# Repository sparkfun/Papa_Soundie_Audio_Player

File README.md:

SparkFun Papa Soundie Audio Player
========================================

[*Papa Soundie Audio Player (14554)*](https://www.sparkfun.com/products/14554)

The SparkFun Papa Soundie is an audio playback device breaking out VS1000D audio codec IC allowing this little board the ability to decode OGG Vorbis and WAV type files. With an SD card for sound storage and a built-in ATmega328P programmed with Arduino you’ll be adding custom sound effects to your project with less hardware and in a familiar programming environment.

The Papa Soundie is the upgraded version of the Little Soundie with similar areas that allow you, the user, to interact with the board but with more customizable options. The top section of this board contains the Arduino Controls. We’ve broken out 2 analog input pins and 7 digital pins, which includes three PWM pins, SPI and I2C communication pins on the ATMEGA328P to easily control audio playback using sensors and other input.

Up to 32 files can be triggered to play from a micro SD card allowing for more storage space than that allowed on the Little Soundie. To play the audio stored in the SD card, plug in a powered speaker to the 3.5mm jack, upload an Arduino sketch the uses the Papa Soundie library, and start jammin'.

_Note: Speakers are required for the Papa Soundie, not headphones. Headphones won’t break anything but you won’t get any sound either._

Repository Contents
-------------------

* **/Documentation** - Data sheets, additional product information
* **/Enclosure** - Enclosure files 
* **/Firmware** - Example code 
* **/Hardware** - Eagle design files (.brd, .sch)
* **/Libraries** - Libraries for use with the Papa Soundie
* **/Production** - Production panel files (.brd)
* **/Software** - Related software for the Papa Soundie

Documentation
--------------
* **[Library](https://github.com/sparkfun/Papa_Soundie_Audio_Player)** - <C> library for the Papa Soundie.
* **[Hookup Guide](https://learn.sparkfun.com/tutorials/papa-soundie-audio-player-hookup-guide)** - Basic hookup guide for the Papa Soundie.
* **[SparkFun Fritzing repo](https://github.com/sparkfun/Fritzing_Parts)** - Fritzing diagrams for SparkFun products.
* **[SparkFun 3D Model repo](https://github.com/sparkfun/3D_Models)** - 3D models of SparkFun products. 
* **[SparkFun Graphical Datasheets](https://github.com/sparkfun/Graphical_Datasheets)** -Graphical Datasheets for various SparkFun products.

License Information
-------------------

This product is _**open source**_! 

Please review the LICENSE.md file for license information. 

If you have any questions or concerns on licensing, please contact techsupport@sparkfun.com.

Distributed as-is; no warranty is given.

- Your friends at SparkFun.

_<COLLABORATION CREDIT>_

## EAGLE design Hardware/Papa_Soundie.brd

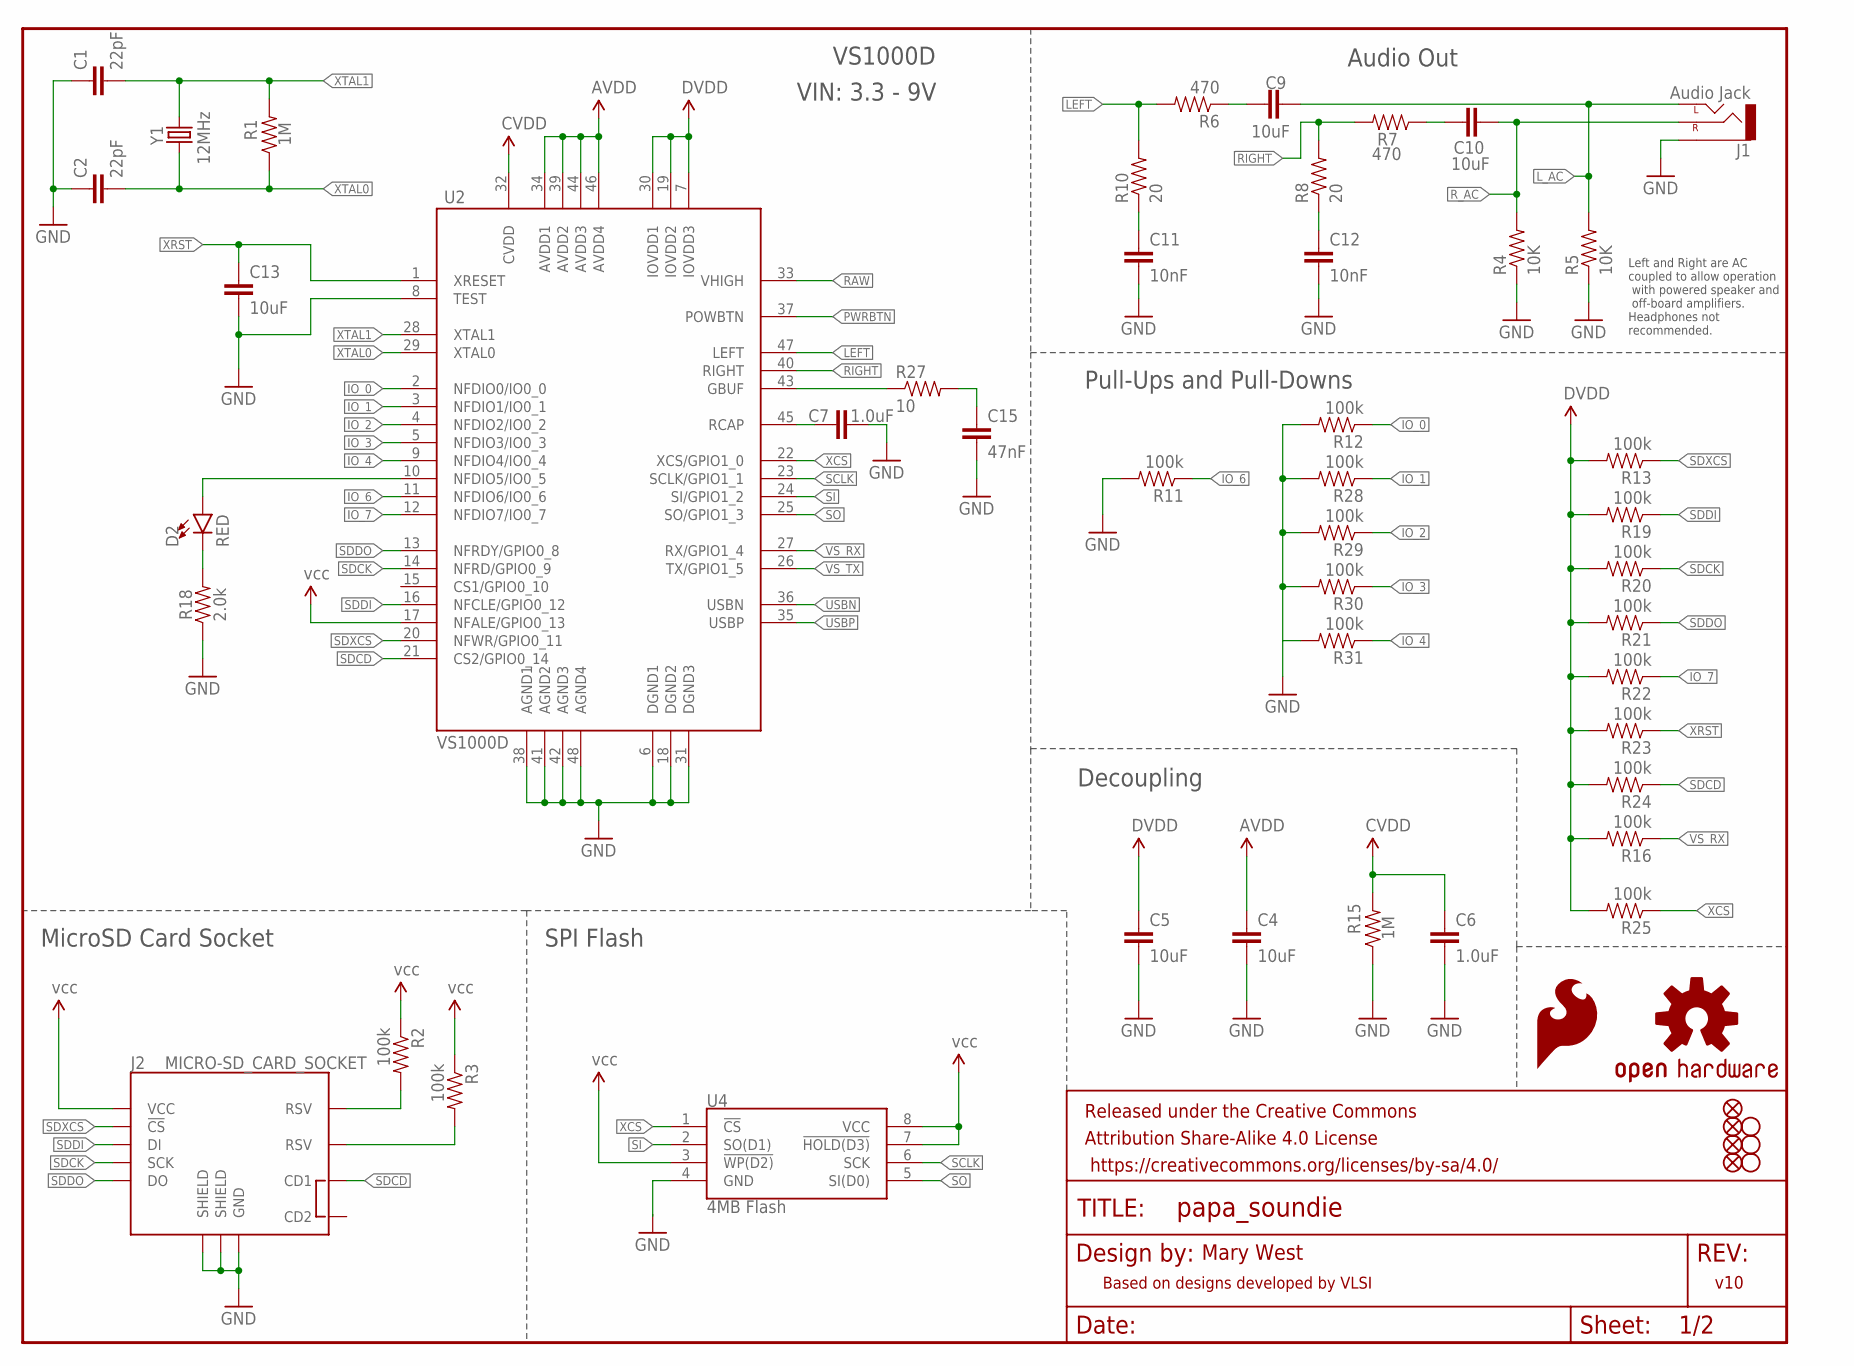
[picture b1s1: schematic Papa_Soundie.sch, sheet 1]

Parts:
C1, C2: 22pF; 0603-CAP
C4, C5: 10uF; 0603
C6, C7: 1.0uF; 0603-CAP
C9, C10, C13: 10uF; 0603-CAP
C11, C12: 10nF; 0603-CAP
C15: 47nF; 0603-CAP
D2: RED; LED-0603
FD1, FD2, FD3, FD4: FIDUCIALUFIDUCIAL; FIDUCIAL-MICRO
FRAME1: FRAME-LETTER; CREATIVE_COMMONS
H1, H2, H3: STAND-OFFTIGHT; STAND-OFF-TIGHT
J1: Audio Jack; AUDIO-JACK-3.5MM-SMD
J2: MICRO-SD_CARD_SOCKET; MICRO-SD-SOCKET
LOGO1: OSHW-LOGOL; OSHW-LOGO-L
LOGO2: SFE_LOGO_FLAME.2_INCH; SFE_LOGO_FLAME_.2
R1, R15: 1M; 0603-RES
R2, R3, R11, R12, R13, R16, R19, R20, R21, R22, R23, R24, R25, R28, R29, R30, R31: 100k; 0603-RES
R4, R5: 10K; 0603-RES
R6, R7: 470; 0603-RES
R8, R10: 20; 0603-RES
R18: 2.0k; 0603
R27: 10; 0603-RES
U2: VS1000D; LQFP-48
U4: 4MB Flash; SO08
Y1: 12MHz; CRYSTAL-SMD-5X3

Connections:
AVDD: C4.1, U2.34 (AVDD1), U2.39 (AVDD2), U2.44 (AVDD3), U2.46 (AVDD4)
CVDD: C6.1, R15.2, U2.32 (CVDD)
DVDD: C5.1, R13.2, R16.2, R19.2, R20.2, R21.2, R22.2, R23.2, R24.2, R25.2, U2.7 (IOVDD3), U2.19 (IOVDD2), U2.30 (IOVDD1)
GBUF: R27.1, U2.43 (GBUF)
GND: C1.1, C2.1, C4.2, C5.2, C6.2, C7.2, C11.2, C12.2, C13.2, C15.2, J1.SLEEVE, J2.GND, J2.GND1 (SHIELD), J2.GND3 (SHIELD), R4.1, R5.1, R11.2, R12.2, R15.1, R18.1, R28.2, R29.2, R30.2, R31.2, U2.6 (DGND1), U2.8 (TEST), U2.18 (DGND2), U2.31 (DGND3), U2.38 (AGND1), U2.41 (AGND2), U2.42 (AGND3), U2.48 (AGND4), U4.4 (GND); also elsewhere on the board
IO_0: R12.1, U2.2 (NFDIO0/IO0_0); also elsewhere on the board
IO_1: R28.1, U2.3 (NFDIO1/IO0_1); also elsewhere on the board
IO_2: R29.1, U2.4 (NFDIO2/IO0_2); also elsewhere on the board
IO_3: R30.1, U2.5 (NFDIO3/IO0_3); also elsewhere on the board
IO_4: R31.1, U2.9 (NFDIO4/IO0_4); also elsewhere on the board
IO_6: R11.1, U2.11 (NFDIO6/IO0_6)
IO_7: R22.1, U2.12 (NFDIO7/IO0_7)
LEFT: R6.2, R10.2, U2.47 (LEFT)
L_AC: C9.2, J1.TIP (LEFT), R5.2; also elsewhere on the board
unnamed: C15.1, R27.2
unnamed: C9.1, R6.1
unnamed: C11.1, R10.1
unnamed: C7.1, U2.45 (RCAP)
unnamed: J2.RSV1 (RSV), R2.2
unnamed: C10.1, R7.1
unnamed: J2.RSV2 (RSV), R3.2
unnamed: C12.1, R8.1
unnamed: D2.C, R18.2
unnamed: D2.A, U2.10 (NFDIO5/IO0_5)
PWRBTN: U2.37 (POWBTN); also elsewhere on the board
RAW: U2.33 (VHIGH); also elsewhere on the board
RIGHT: R7.2, R8.2, U2.40 (RIGHT)
R_AC: C10.2, J1.RING (RIGHT), R4.2; also elsewhere on the board
SCLK: U2.23 (SCLK/GPIO1_1), U4.6 (SCK)
SDCD: J2.CD1, R24.1, U2.21 (CS2/GPIO0_14)
SDCK: J2.SCLK (SCK), R20.1, U2.14 (NFRD/GPIO0_9)
SDDI: J2.DI, R19.1, U2.16 (NFCLE/GPIO0_12)
SDDO: J2.DO, R21.1, U2.13 (NFRDY/GPIO0_8)
SDXCS: J2.CS (!CS), R13.1, U2.20 (NFWR/GPIO0_11)
SI: U2.24 (SI/GPIO1_2), U4.2 (SO(D1))
SO: U2.25 (SO/GPIO1_3), U4.5 (SI(D0))
USBN: U2.36 (USBN); also elsewhere on the board
USBP: U2.35 (USBP); also elsewhere on the board
VCC: J2.VCC, R2.1, R3.1, U2.17 (NFALE/GPIO0_13), U4.3 (!WP(D2)), U4.7 (!HOLD(D3)), U4.8 (VCC); also elsewhere on the board
VS_RX: R16.1, U2.27 (RX/GPIO1_4); also elsewhere on the board
VS_TX: U2.26 (TX/GPIO1_5); also elsewhere on the board
XCS: R25.1, U2.22 (XCS/GPIO1_0), U4.1 (!CS)
XRST: C13.1, R23.1, U2.1 (XRESET)
XTAL0: C2.2, R1.1, U2.29 (XTAL0), Y1.1
XTAL1: C1.2, R1.2, U2.28 (XTAL1), Y1.3 (2)

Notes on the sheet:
Mary West
v10
Decoupling
Left and Right are AC coupled to allow operation with powered speaker and off-board amplifiers. Headphones not recommended.
Based on designs developed by VLSI
Audio Out
MicroSD Card Socket
Pull-Ups and Pull-Downs
SPI Flash
VS1000D
VIN: 3.3 - 9V

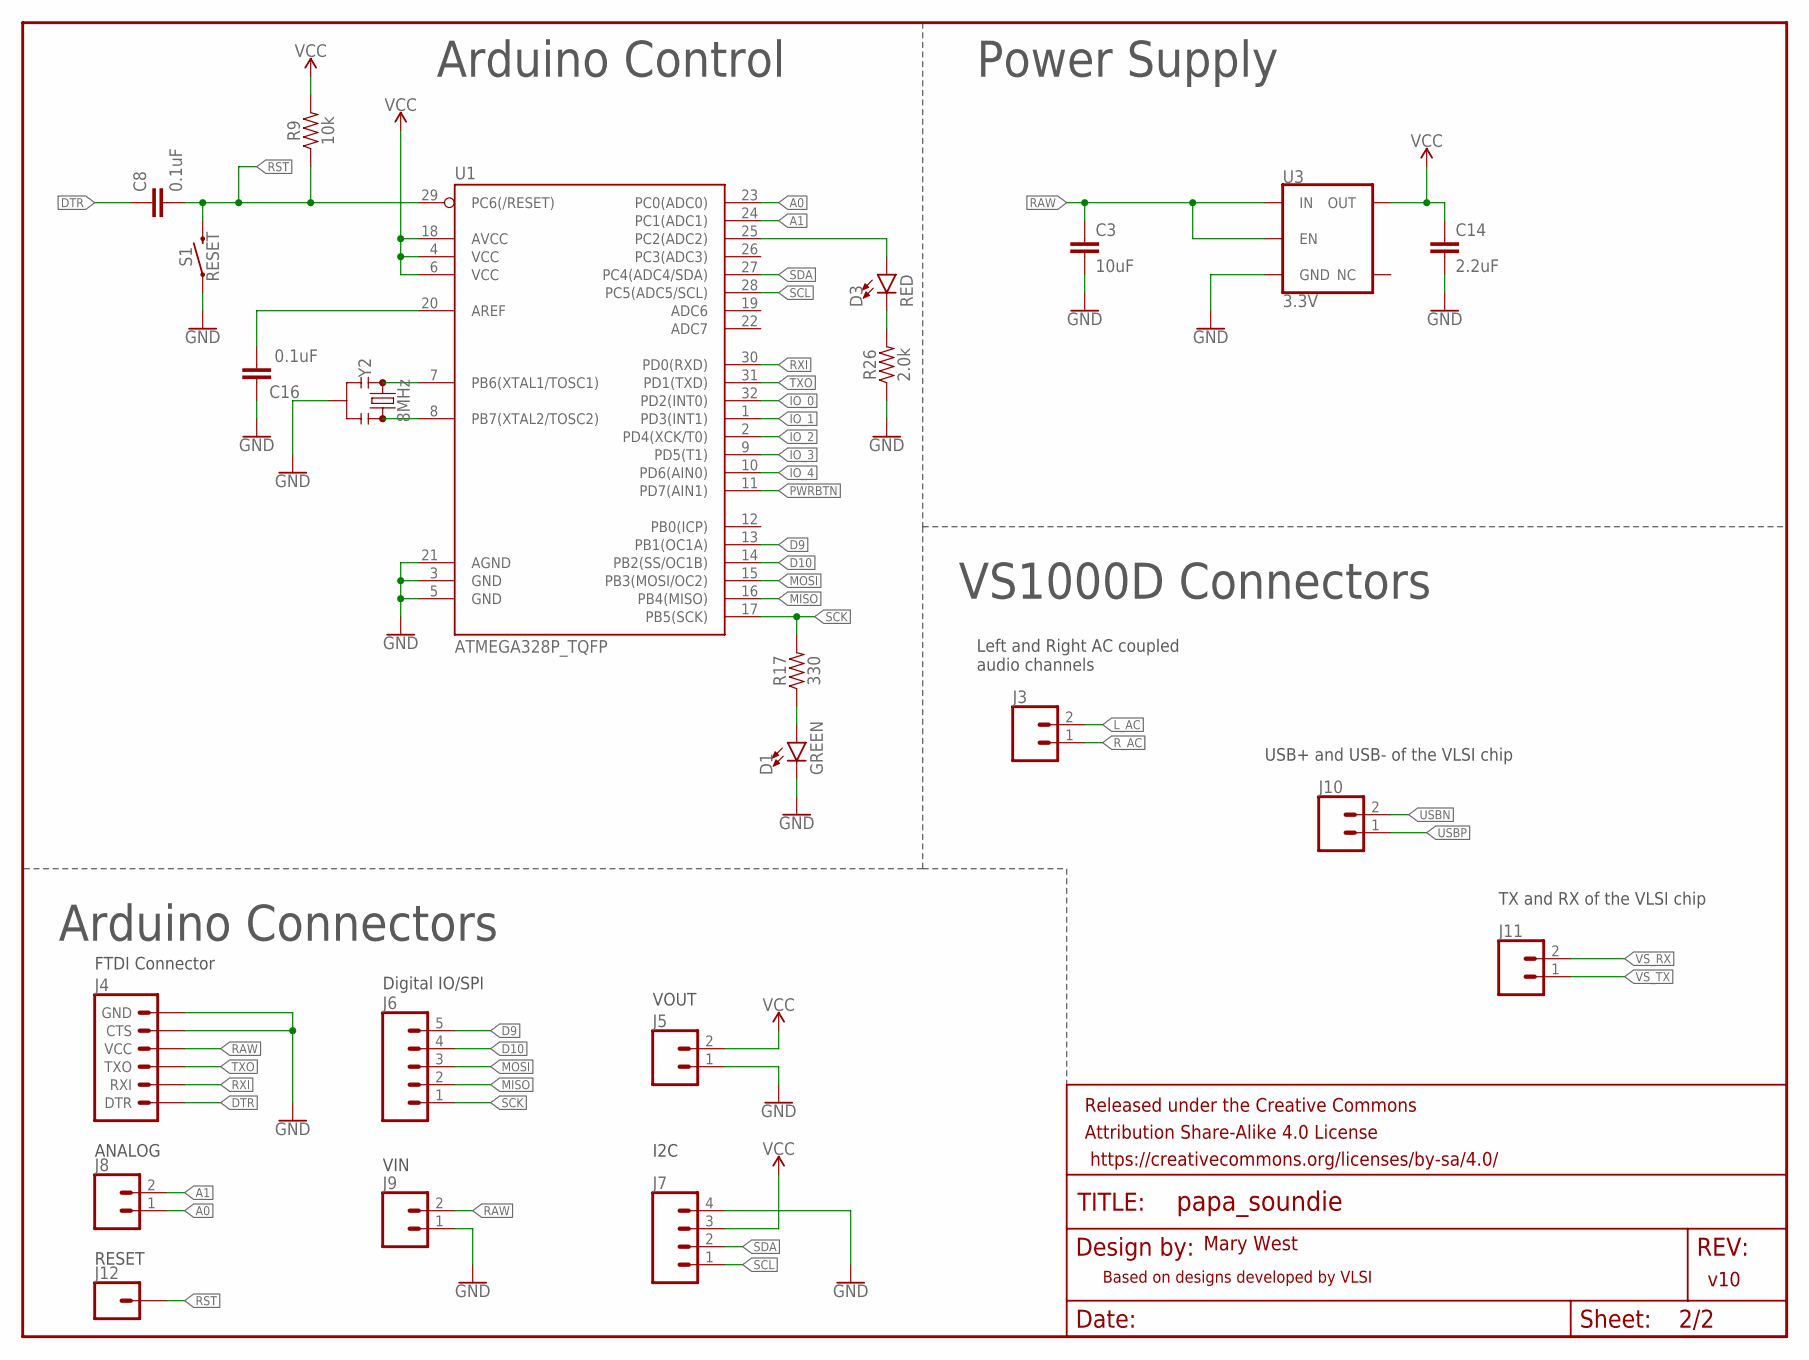
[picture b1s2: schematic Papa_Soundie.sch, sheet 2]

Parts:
C3: 10uF; 0603
C8, C16: 0.1uF; 0603
C14: 2.2uF; 0603
D1: GREEN; LED-0603
D3: RED; LED-0603
FRAME2: FRAME-LETTER; CREATIVE_COMMONS
J3, J5, J8, J9, J10, J11: CONN_02; 1X02
J4: 6_PIN_SERIAL_TARGETSILK; 6_PIN_SERIAL_TARGET_SIDE_W_SILK
J6: CONN_05; 1X05
J7: CONN_04; 1X04
J12: CONN_01; 1X01
R9: 10k; 0603
R17: 330; 0603
R26: 2.0k; 0603
S1: RESET; TACTILE_SWITCH_SMD_5.2MM
U1: ATMEGA328P_TQFP; TQFP32-08
U3: 3.3V; SOT23-5
Y2: 8MHz; RESONATOR-SMD-3.2X1.3

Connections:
A0: J8.1, U1.23 (PC0(ADC0))
A1: J8.2, U1.24 (PC1(ADC1))
D9: J6.5, U1.13 (PB1(OC1A))
D10: J6.4, U1.14 (PB2(SS/OC1B))
DTR: C8.1, J4.P$1 (DTR)
GND: C3.2, C14.2, C16.1, D1.C, J4.P$5 (CTS), J4.P$6 (GND), J5.1, J7.4, J9.1, R26.1, S1.1, U1.3 (GND), U1.5 (GND), U1.21 (AGND), U3.2 (GND), Y2.2; also elsewhere on the board
IO_0: U1.32 (PD2(INT0)); also elsewhere on the board
IO_1: U1.1 (PD3(INT1)); also elsewhere on the board
IO_2: U1.2 (PD4(XCK/T0)); also elsewhere on the board
IO_3: U1.9 (PD5(T1)); also elsewhere on the board
IO_4: U1.10 (PD6(AIN0)); also elsewhere on the board
L_AC: J3.2; also elsewhere on the board
MISO: J6.2, U1.16 (PB4(MISO))
MOSI: J6.3, U1.15 (PB3(MOSI/OC2))
unnamed: U1.7 (PB6(XTAL1/TOSC1)), Y2.1
unnamed: U1.8 (PB7(XTAL2/TOSC2)), Y2.3
unnamed: D3.A, U1.25 (PC2(ADC2))
unnamed: D3.C, R26.2
unnamed: C16.2, U1.20 (AREF)
unnamed: D1.A, R17.1
PWRBTN: U1.11 (PD7(AIN1)); also elsewhere on the board
RAW: C3.1, J4.P$4 (VCC), J9.2, U3.1 (IN), U3.3 (EN); also elsewhere on the board
RST: C8.2, J12.1, R9.1, S1.3 (2), U1.29 (PC6(/RESET))
RXI: J4.P$3 (RXI), U1.30 (PD0(RXD))
R_AC: J3.1; also elsewhere on the board
SCK: J6.1, R17.2, U1.17 (PB5(SCK))
SCL: J7.1, U1.28 (PC5(ADC5/SCL))
SDA: J7.2, U1.27 (PC4(ADC4/SDA))
TXO: J4.P$2 (TXO), U1.31 (PD1(TXD))
USBN: J10.2; also elsewhere on the board
USBP: J10.1; also elsewhere on the board
VCC: C14.1, J5.2, J7.3, R9.2, U1.4 (VCC), U1.6 (VCC), U1.18 (AVCC), U3.5 (OUT); also elsewhere on the board
VS_RX: J11.2; also elsewhere on the board
VS_TX: J11.1; also elsewhere on the board

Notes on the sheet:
Arduino Control
Mary West
v10
Power Supply
VS1000D Connectors
Arduino Connectors
Left and Right AC coupled audio channels
USB+ and USB- of the VLSI chip
TX and RX of the VLSI chip
VOUT
I2C
Digital IO/SPI
FTDI Connector
ANALOG
VIN
RESET
Based on designs developed by VLSI

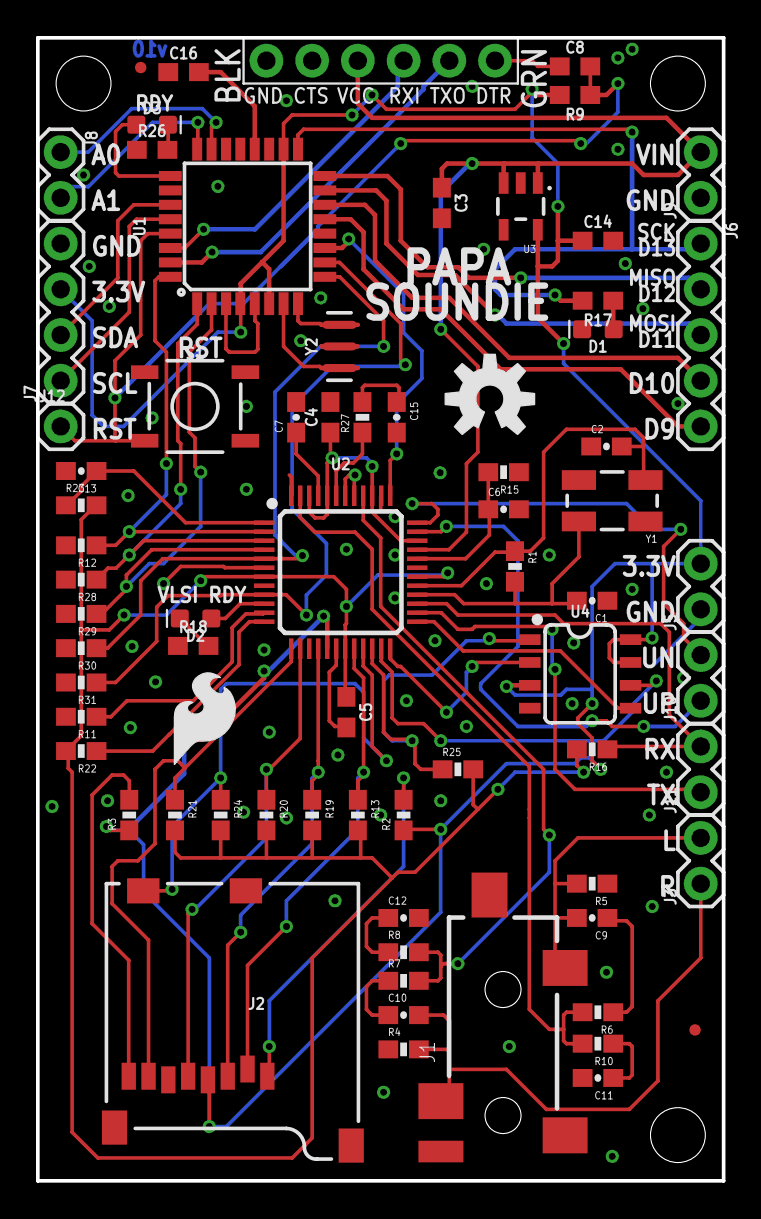
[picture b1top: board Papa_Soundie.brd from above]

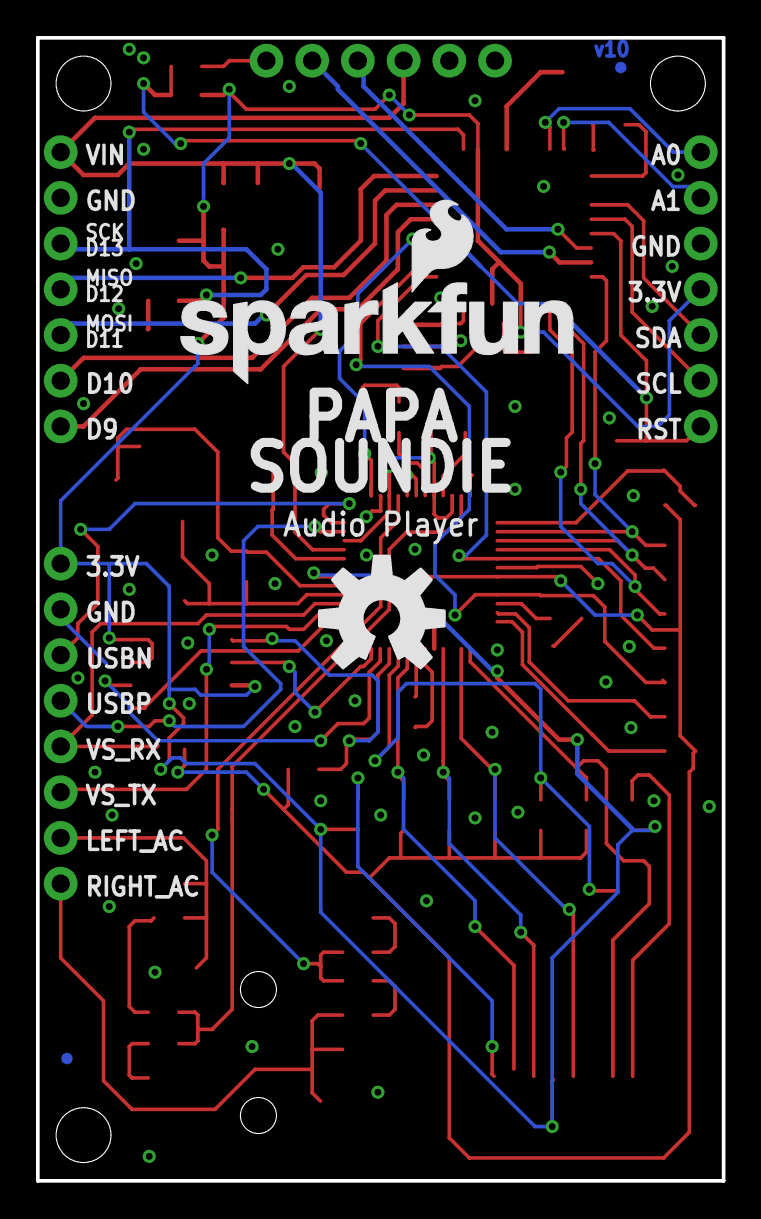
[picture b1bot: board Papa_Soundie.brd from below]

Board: 2 copper layers, 38.1 x 63.5 mm, 82 parts (4 on the bottom side), 64 nets.

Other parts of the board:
FRAME3: FRAME-LETTER; CREATIVE_COMMONS
LOGO3: OSHW-LOGOL; OSHW-LOGO-M
LOGO6: SFE_LOGO_NAME_FLAME.1_INCH; SFE_LOGO_NAME_FLAME_.2

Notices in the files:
parts and their libraries:
SparkFun-Aesthetics: Licensing: Creative Commons ShareAlike 4.0 International - https://creativecommons.org/licenses/by-sa/4.0
SparkFun-Aesthetics: Released under the Creative Commons Attribution Share-Alike 4.0 License
SparkFun-Aesthetics: https://creativecommons.org/licenses/by-sa/4.0
